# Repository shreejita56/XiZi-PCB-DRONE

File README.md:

# PCB-Drone

So I made a custom PCB based on Esp32 . It holds an IMU and a Barometer for control . It has a normal 4 Motor Layout 2 motors will move  clock wise and 2 will be  anti-clock wise direction. Same direction motor will be diagonally apposite to each other. It have  used a 3.7V battery for power and a boot converter so that I can provide 5V to the Motors as we are using  ESP32 so we could controle it by our phone through bluetooth  .I have also design a  controller , So that you could connect and controle the Bionic-Bird through your phone.

So I have a USB-C and battery pin (3.7V) then it is commonly connected to power with diodes for reverse polarity then It goes to a 3.3V voltage regulator (AP63203WU) with Reverse Polarity Protection and Pi Filter for sensors and ESp32  . and 5V regulator (MT3608) for motors . Then 3.3v it goes to IMU (MPU-6050) Barometer (BMP280) then through I2c these data are transferred to ESP32 where computation takes place and through Logic-Level Enhancement Mode MOSFET(AO3400A) circuit it amplifies  the PWN signal to 5V for the motors to work  

## Features

- Base on ESP32 Module
- Has IMU (MPU_6050)
- Has a Barometer (BMP280)
- Uses 4 8520 Motors 

## Components BOM

### 1. JLCPCB Manufacturing & Assembly Services
| Charge Description | Details / Notes | Cost ($) |
| :--- | :--- | :---: |
| **Components Cost** | 26 Matched Part Lines | $64.35 |
| **Setup Fee** | SMT Line Assembly Setup | $25.56 |
| **Stencil Fee** | SMT Laser Stencil | $8.21 |
| **Feeders Loading Fee** | Component Feeder Setup | $33.66 |
| **SMT Assembly** | Automated SMT Placement | $1.23 |
| **Hand-Soldering Labor Fee** | Through-hole / Manual Soldering | $3.58 |
| **Manual Assembly** | Specialized Component Insertion | $0.46 |
| **X-Ray Inspection** | BGA / QFN Joint Verification | $3.28 |
| **Packaging Fee** | Protective ESD Packaging | $0.50 |
| **Engineering Fee** | DFM / CAM File Verification | $4.00 |
| **Via Covering** | Tent / Plugged Vias | $0.00 |
| **PCB Fabrication Board Fee** | Raw Printed Circuit Board Cost | $9.90 |
| **PCB Shipping** | Express Courier to Destination | $11.53 |

---

### 2. External Hardware & Accessories
| Item | Description / Details | Qty | Link | Cost ($) |
| :--- | :--- | :---: | :---: | :---: |
| **8520 Coreless Motor** | Magnetic Micro Coreless Motor Set (2x CW, 2x CCW) | 1 Set | [Robu.in Link](https://robu.in/product/8520-magnetic-micro-coreless-motor-for-micro-quadcopters-2xcw-2xccw/) | $4.93 |
| **3.7V Battery** | KP Original 802540 1200mAh Single-Cell LiPo Battery | 1 Pcs | [Zbotic Link](https://zbotic.in/product/kp-original-802540-1200mah-3-7vsingle-cell-rechargeable-lipo-battery/) | $3.46 |

---

## 🧩 Complete Component Bill of Materials (BOM)

| Designator | Description / Value | Footprint | Qty | Price ($) | Part Details / Link |
| :--- | :--- | :--- | :---: | :---: | :--- |
| **C2** | 47uF 450V Electrolytic | 0201 | 2 | $1.333 | [KM476M450K25RR0VH2FP0](https://jlcpcb.com/partdetail/3127-KM476M450K25RR0VH2FP0/C2746) |
| **C3, C11, C18, C19** | 10uF 6.3V X5R | 0201 | 40 | $1.172 | [CL10A106MQ8NNNC](https://jlcpcb.com/partdetail/2043-CL10A106MQ8NNNC/C1691) |
| **C4, C13, C14** | 100nF 10V X5R | 0201 | 40 | $0.292 | [GRM033R61A104KE15D](https://jlcpcb.com/partdetail/MurataElectronics-GRM033R61A104KE15D/C76934) |
| **C5, C6** | 22uF 10V X5R | 0201 | 16 | $5.0256 | [1206X226K100NT](https://jlcpcb.com/partdetail/2211-1206X226K100NT/C1859) |
| **C9, C10, C12** | 0.1uF 10V X5R | 0201 | 40 | $0.236 | [0201X104K100NT](https://jlcpcb.com/partdetail/270391-0201X104K100NT/C284966) |
| **C7, C8, C15, C16** | 50nF Capacitors | 0201 | 8 | $6.532 | [LHC503SA2K0042NWB](https://jlcpcb.com/partdetail/launchip-LHC503SA2K0042NWB/C49233446) |
| **C1X1 - C6X1** | 1uF / 100nF Caps | 0805 | 22 | $0.3982 | [GZ2012D220TF](https://jlcpcb.com/partdetail/Sunlord-GZ2012D220TF/C1009) |
| **D1, D3** | LED Indicator | 0201 | 8 | $0.5448 | [XL0201SURC](https://jlcpcb.com/partdetail/XINGLIGHT-XL0201SURC/C3646923) |
| **D2** | Diode | 0201 | 2 | $0.3944 | [HIR204C](https://jlcpcb.com/partdetail/EverlightElec-HIR204C/C5118) |
| **D4, D5, D6, D7** | Schottky Diode | 0201 | 20 | $0.038 | [0201WMJ010JTEE](https://jlcpcb.com/partdetail/25797-0201WMJ010JTEE/C25054) |
| **F1** | Polyfuse | 0201 | 20 | $0.038 | [0201WMJ010JTEE](https://jlcpcb.com/partdetail/25797-0201WMJ010JTEE/C25054) |
| **D8** | 1N4001 Diode | DO-41 | 4 | $0.0776 | [1N4001](https://jlcpcb.com/partdetail/49200031-1N4001/C47018536) |
| **L1** | 2.2uH Power Inductor | 0201 | 20 | $0.750 | [CY43_22UH](https://jlcpcb.com/partdetail/SHOUHAN-CY43_22UH/C2929416) |
| **L2** | 4.7uH Inductor | 0603 | 20 | $0.414 | [SDFL1608Q4R7KTF](https://jlcpcb.com/partdetail/Sunlord-SDFL1608Q4R7KTF/C1034) |
| **Q1** | AO3401A P-Ch MOSFET | SOT-23 | 6 | $0.5688 | [AO3401A](https://jlcpcb.com/partdetail/Alpha_OmegaSemicon-AO3401A/C15127) |
| **Q2, Q3, Q4, Q5** | AO3400A N-Ch MOSFET | SOT-23 | 12 | $1.008 | [AO3400A](https://jlcpcb.com/partdetail/Alpha_OmegaSemicon-AO3400A/C20917) |
| **R1, R2** | 33 Ohm Resistor | 0201 | 20 | $0.062 | [0201WMJ0330TEE](https://jlcpcb.com/partdetail/416306-0201WMJ0330TEE/C423356) |
| **R3, R4** | 50K Resistor | 0201 | 6 | $0.7632 | [GL3549](https://jlcpcb.com/partdetail/10622-GL3549/C10083) |
| **R6, R7** | 1K Resistor | 0201 | 20 | $0.050 | [0201WMF1001TEE](https://jlcpcb.com/partdetail/259895-0201WMF1001TEE/C270365) |
| **R8, R10, R12, R14** | 100 Ohm Resistor | 0201 | 20 | $0.056 | [RC01W1000FT](https://jlcpcb.com/partdetail/288566-RC01W1000FT/C304499) |
| **R9, R11, R13, R15** | 10K Resistor | 0201 | 20 | $0.086 | [CR0201FH1002G](https://jlcpcb.com/partdetail/LIZElec-CR0201FH1002G/C100126) |
| **R1_1, R2_1** | 10K / 100 Ohm | 0805 | 6 | $0.5364 | [FSMD050_0805R](https://jlcpcb.com/partdetail/FuzetecTech-FSMD050_0805R/C181350) |
| **U1** | MT3608 Boost Regulator | SOT-23-6 | 5 | $0.5665 | [MT3608](https://jlcpcb.com/partdetail/XI_AN_AerosemiTech-MT3608/C84817) |
| **U2** | AP63203WU Buck Regulator | TSOT-23-6 | 2 | $2.2268 | [AP63203QWU7](https://jlcpcb.com/partdetail/DiodesIncorporated-AP63203QWU7/C5248536) |
| **U3** | MPU-6050 6-Axis IMU Sensor | QFN-24 | 2 | $29.0122 | [MPU6050](https://jlcpcb.com/partdetail/TDKInvenSense-MPU6050/C24112) |
| **U4** | BMP280 Barometric Pressure Sensor | LGA-8 | 2 | $5.2442 | [BMP388 / BMP280](https://jlcpcb.com/partdetail/BoschSensortec-BMP388/C779278) |
| **U5** | ESP32-S3-WROOM-1 Wi-Fi/BT MCU | Module | 2 | $10.327 | [ESP32_S3_WROOM_1N16R8](https://jlcpcb.com/partdetail/3198300-ESP32_S3_WROOM_1N16R8/C2913202) |
| **J1** | USB Type-C Receptacle 16P | USB-C | - | - | Hand Assembly / Manual |
| **J2** | Pin Header Connector | JST-EH 2.5mm | - | - | Through Hole |
| **M1, M2, M3, M4** | Motor Drive Outputs | 1x02 Pin Header | - | - | Through Hole |
| **SW1, SW2** | Push Button Switches | PTS810 | - | - | SMT / Manual |

---

---

## 📊 Summary & Total Cost

| Category | Total Cost (USD) |
| :--- | :---: |
| **PCBA Manufacturing & Components (26 Items)** | **$154.73** |
| **PCB Shipping (JLCPCB)** | **$11.53** |
| **External Motors (8520 Coreless Motor Set)** | **$4.93** |
| **3.7V LiPo Battery (1200mAh)** | **$3.46** |
| **Grand Total** | **`$174.65`** |

### Schematic

###  PCB Design

###  3D Design

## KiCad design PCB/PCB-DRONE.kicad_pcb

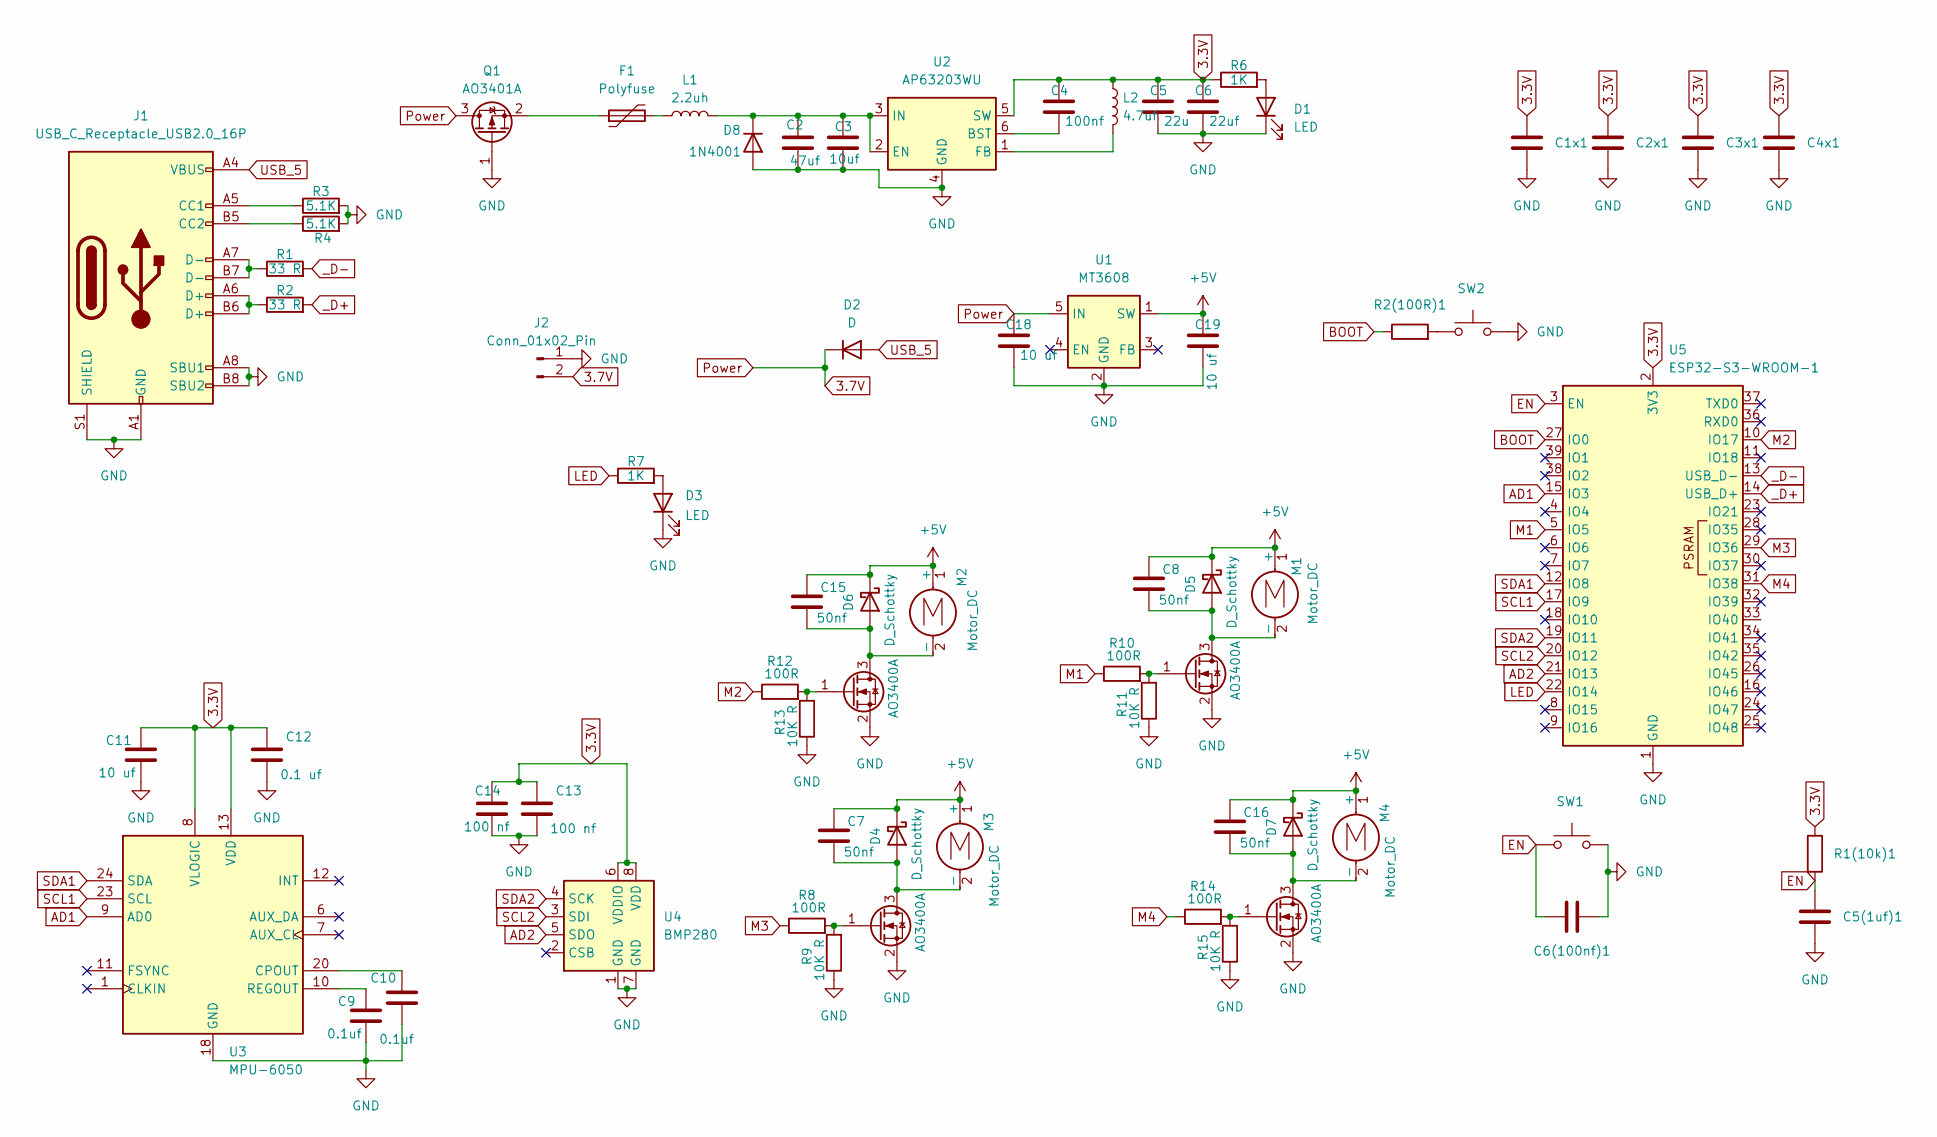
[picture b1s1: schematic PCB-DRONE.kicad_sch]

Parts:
C1x1, C2x1, C3x1, C4x1, C5(1uf)1, C6(100nf)1: C; C_0805_2012Metric
C2: 47uf; C_0201_0603Metric
C3: 10uf; C_0201_0603Metric
C4: 100nf; C_0201_0603Metric
C5: 22u; C_0201_0603Metric
C6: 22uf; C_0201_0603Metric
C7, C8, C15, C16: 50nf; C_0201_0603Metric
C9, C10: 0.1uf; C_0201_0603Metric
C11, C18, C19: 10 uf; C_0201_0603Metric
C12: 0.1 uf; C_0201_0603Metric
C13, C14: 100 nf; C_0201_0603Metric
D1, D3: LED; LED_0201_0603Metric
D2: D; D_0201_0603Metric
D4, D5, D6, D7: D_Schottky; D_0201_0603Metric
D8: 1N4001; D_DO-41_SOD81_P5.08mm_Vertical_KathodeUp
F1: Polyfuse; C_0201_0603Metric
J1: USB_C_Receptacle_USB2.0_16P; USB_C_Receptacle_G-Switch_GT-USB-7010ASV
J2: Conn_01x02_Pin; JST_EH_B2B-EH-A_1x02_P2.50mm_Vertical
L1: 2.2uh; L_0201_0603Metric
L2: 4.7uf; L_0603_1608Metric
M1, M2, M3, M4: Motor_DC; PinHeader_1x02_P2.54mm_Vertical
Q1: AO3401A; SOT-23
Q2, Q3, Q4, Q5: AO3400A; SOT-23
R1, R2: 33 R; R_0201_0603Metric_Pad0.64x0.40mm_HandSolder
R1(10k)1, R2(100R)1: R; R_0805_2012Metric
R3, R4: 5.1K; R_0201_0603Metric_Pad0.64x0.40mm_HandSolder
R6, R7: 1K; R_0201_0603Metric_Pad0.64x0.40mm_HandSolder
R8, R10, R12, R14: 100R; R_0201_0603Metric
R9, R11, R13, R15: 10K R; R_0201_0603Metric
SW1, SW2: SW_Push; SW_SPST_PTS810
U1: MT3608; SOT-23-6
U2: AP63203WU; TSOT-23-6
U3: MPU-6050; InvenSense_QFN-24_4x4mm_P0.5mm
U4: BMP280; Bosch_LGA-8_2x2.5mm_P0.65mm_ClockwisePinNumbering
U5: ESP32-S3-WROOM-1

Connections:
3.3V: C1x1.1, C2x1.1, C3x1.1, C4.1, C4x1.1, C5.1, C6.1, C11.1, C12.1, C13.1, C14.1, L2.1, R1(10k)1.1, R6.1, U2.5 (SW), U3.8 (VLOGIC), U3.13 (VDD), U4.6 (VDDIO), U4.8 (VDD), U5.2 (3V3)
3.7V: C18.1, D2.1 (K), J2.2, Q1.3 (D), U1.5 (IN)
+5V: C7.1, C8.1, C15.1, C16.1, C19.1, D4.1 (K), D5.1 (K), D6.1 (K), D7.1 (K), M1.1 (+), M2.1 (+), M3.1 (+), M4.1 (+), U1.1 (SW)
AD1: U3.9 (AD0), U5.15 (IO3)
AD2: U4.5 (SDO), U5.21 (IO13)
BOOT: R2(100R)1.1, U5.27 (IO0)
EN: C5(1uf)1.1, C6(100nf)1.1, R1(10k)1.2, SW1.1, U5.3 (EN)
GND: C1x1.2, C2.2, C2x1.2, C3.2, C3x1.2, C4x1.2, C5.2, C5(1uf)1.2, C6.2, C6(100nf)1.2, C9.2, C10.2, C11.2, C12.2, C13.2, C14.2, C18.2, C19.2, D1.1 (K), D3.1 (K), D8.2 (A), J1.A1 (GND), J1.A8 (SBU1), J1.A12 (GND), J1.B1 (GND), J1.B8 (SBU2), J1.B12 (GND), J1.S1 (SHIELD), J2.1, Q1.1 (G), Q2.2 (S), Q3.2 (S), Q4.2 (S), Q5.2 (S), R3.2, R4.2, R9.1, R11.1, R13.1, R15.1, SW1.2, SW2.2, U1.2 (GND), U2.4 (GND), U3.18 (GND), U4.1 (GND), U4.7 (GND), U5.1 (GND), U5.40 (GND), U5.41 (GND)
LED: R7.1, U5.22 (IO14)
M1: R10.1, U5.5 (IO5)
M2: R12.1, U5.10 (IO17)
M3: R8.1, U5.29 (IO36)
M4: R14.1, U5.31 (IO38)
unnamed: D1.2 (A), R6.2
unnamed: D3.2 (A), R7.2
unnamed: C7.2, D4.2 (A), M3.2 (-), Q2.3 (D)
unnamed: C8.2, D5.2 (A), M1.2 (-), Q3.3 (D)
unnamed: C15.2, D6.2 (A), M2.2 (-), Q4.3 (D)
unnamed: C16.2, D7.2 (A), M4.2 (-), Q5.3 (D)
unnamed: C2.1, C3.1, D8.1 (K), L1.2, U2.2 (EN), U2.3 (IN)
unnamed: F1.2, L1.1
unnamed: J1.A5 (CC1), R3.1
unnamed: J1.B5 (CC2), R4.1
unnamed: J1.A6 (D+), J1.B6 (D+), R2.1
unnamed: J1.A7 (D-), J1.B7 (D-), R1.1
unnamed: F1.1, Q1.2 (S)
unnamed: Q2.1 (G), R8.2, R9.2
unnamed: Q3.1 (G), R10.2, R11.2
unnamed: Q4.1 (G), R12.2, R13.2
unnamed: Q5.1 (G), R14.2, R15.2
unnamed: R2(100R)1.2, SW2.1
unnamed: C4.2, U2.6 (BST)
unnamed: L2.2, U2.1 (FB)
unnamed: C10.1, U3.20 (CPOUT)
unnamed: C9.1, U3.10 (REGOUT)
SCL1: U3.23 (SCL), U5.17 (IO9)
SCL2: U4.3 (SDI), U5.20 (IO12)
SDA1: U3.24 (SDA), U5.12 (IO8)
SDA2: U4.4 (SCK), U5.19 (IO11)
USB_5: D2.2 (A), J1.A4 (VBUS), J1.A9 (VBUS), J1.B4 (VBUS), J1.B9 (VBUS)
_D+: R2.2, U5.14 (USB_D+)
_D-: R1.2, U5.13 (USB_D-)

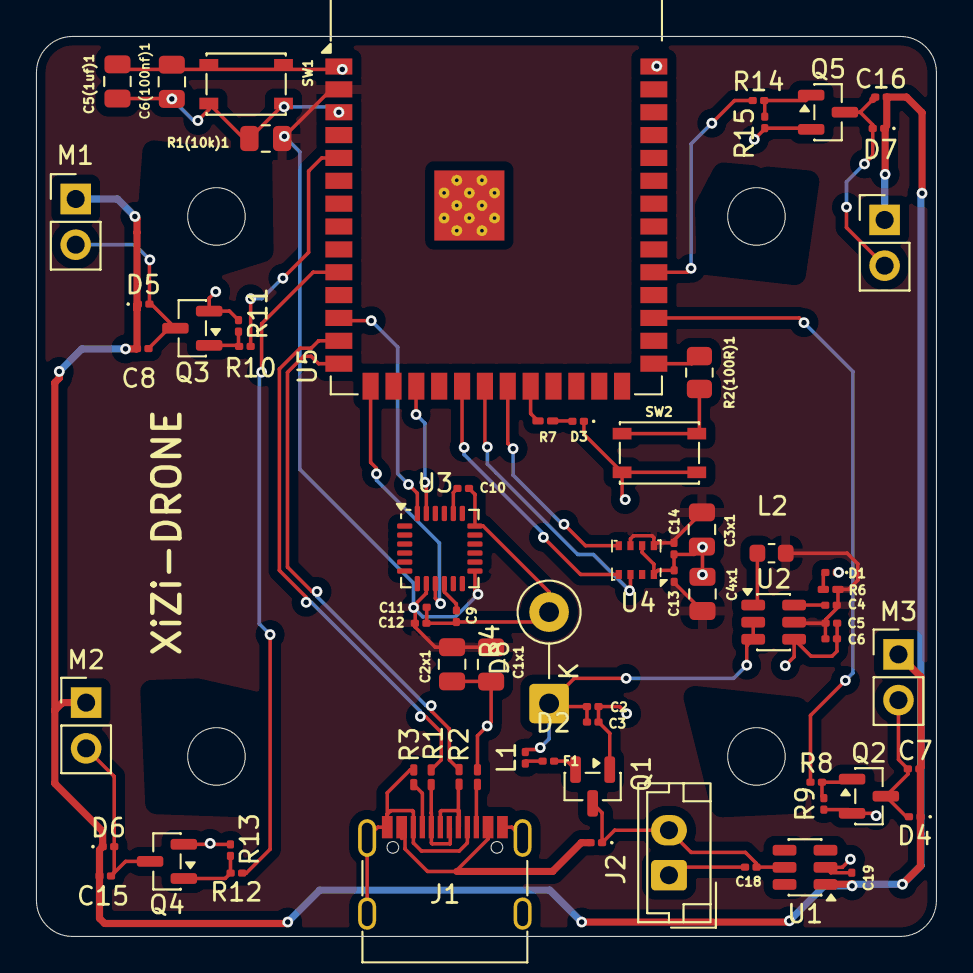
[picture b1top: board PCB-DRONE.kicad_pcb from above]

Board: 2 copper layers, 50.0 x 50.0 mm, 68 parts (0 on the bottom side), 42 nets.

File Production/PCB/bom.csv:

Designator,Footprint,Quantity,Value,LCSC Part #
"C10, C9",0201,2,0.1uf,
"C11, C18, C19",0201,3,10 uf,
C12,0201,1,0.1 uf,
"C13, C14",0201,2,100 nf,
"C15, C16, C7, C8",0201,4,50nf,
"C1X1, C2X1, C3X1, C4X1, C5(1UF)1, C6(100NF)1",0805,6,C,
C2,0201,1,47uf,
C3,0201,1,10uf,
C4,0201,1,100nf,
C5,0201,1,22u,
C6,0201,1,22uf,
"D1, D3",0201,2,LED,
D2,0201,1,D,
"D4, D5, D6, D7",0201,4,D_Schottky,
D8,D_DO-41_SOD81_P5.08mm_Vertical_KathodeUp,1,1N4001,
F1,0201,1,Polyfuse,
J1,USB_C_Receptacle_G-Switch_GT-USB-7010ASV,1,USB_C_Receptacle_USB2.0_16P,
J2,JST_EH_B2B-EH-A_1x02_P2.50mm_Vertical,1,Conn_01x02_Pin,
L1,0201,1,2.2uh,
L2,0603,1,4.7uf,
"M1, M2, M3, M4",PinHeader_1x02_P2.54mm_Vertical,4,Motor_DC,
Q1,SOT-23,1,AO3401A,
"Q2, Q3, Q4, Q5",SOT-23,4,AO3400A,
"R1, R2",0201,2,33 R,
"R1(10K)1, R2(100R)1",0805,2,R,
"R10, R12, R14, R8",0201,4,100R,
"R11, R13, R15, R9",0201,4,10K R,
"R3, R4",0201,2,5.1K,
"R6, R7",0201,2,1K,
"SW1, SW2",SW_SPST_PTS810,2,SW_Push,
U1,SOT-23-6,1,MT3608,
U2,TSOT-23-6,1,AP63203WU,
U3,InvenSense_QFN-24_4x4mm_P0.5mm,1,MPU-6050,
U4,Bosch_LGA-8_2x2.5mm_P0.65mm_ClockwisePinNumbering,1,BMP280,
U5,ESP32-S3-WROOM-1,1,ESP32-S3-WROOM-1,
